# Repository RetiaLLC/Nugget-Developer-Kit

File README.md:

# WiFi Nugget Developer Kit v2.2
This repository contains KiCAD design files for the WiFi Nugget Developer Kit PCB.  The current version of this release is `2.2`.
This kit is designed to teach beginners basic hardware assembly skills, and features both through-hole and surface mount components.
<p align="center">
  <br>
  
  <br>
  <b>ESP32-S2 DevKit Components</b>
  <br>
  <br>
</p>

## Features
This kit is designed to work with the [Wemos "mini" form factor](https://www.wemos.cc/en/latest/), and accomodates breakouts for the ESP8266, ESP32-S2, and some other Espressif based board designs.
The developer kit includes:

- **Buttons** (D-Pad style, 4 Buttons)
- **RGB LED** (WS2812B NeoPixel)
- **WiFi Microcontroller** ([D1](https://www.wemos.cc/en/latest/d1/index.html)/[S2](https://www.wemos.cc/en/latest/s2/index.html)/[C3](https://www.wemos.cc/en/latest/c3/index.html) Mini)
- **Screen** (SH1106 1.3" OLED)
- **Expansion Headers** 
- **Screw Assembly*** (M2.5 Screws / Threaded Inserts)
- **3D Printed Case***

\* *We ditched the screw assembly on newer Nuggets, which use a snap-fit case.  You can find links to our case designs below.*

## Resources
- [Assembly Guide]()
- [3D printed cases](https://github.com/HakCat-Tech/WiFi-Nugget-Cases)

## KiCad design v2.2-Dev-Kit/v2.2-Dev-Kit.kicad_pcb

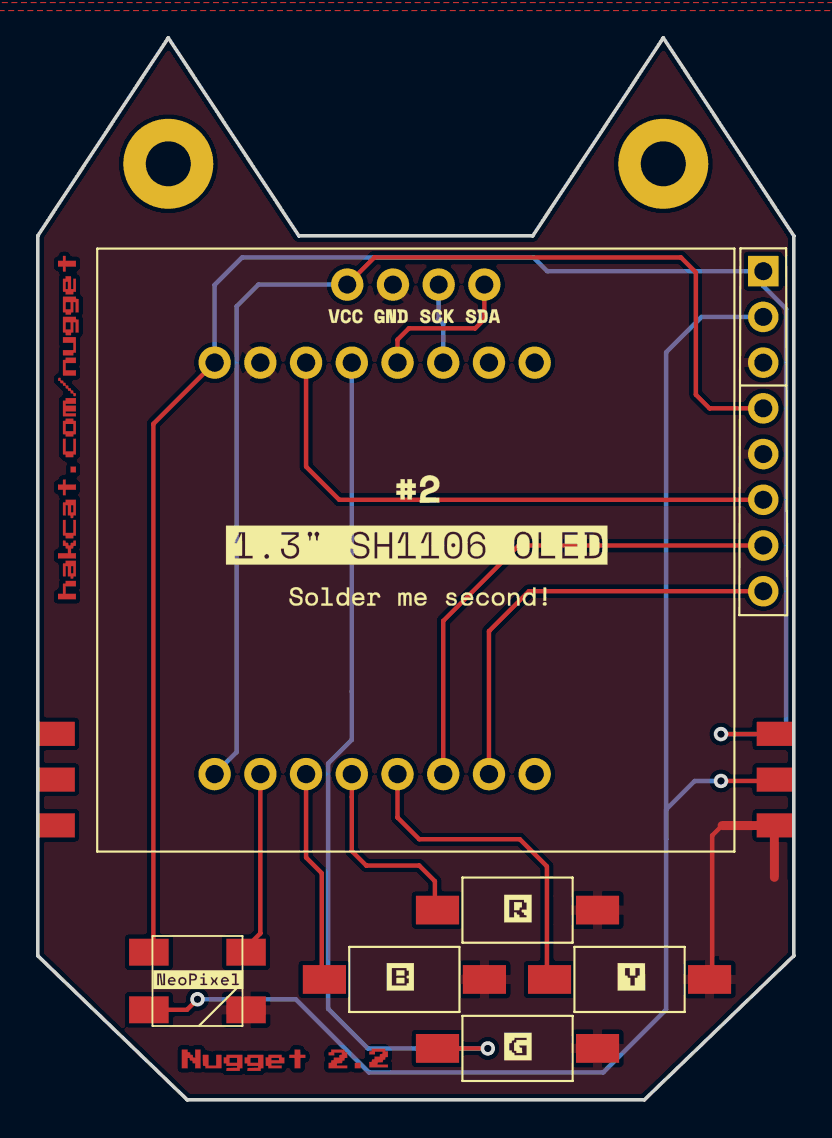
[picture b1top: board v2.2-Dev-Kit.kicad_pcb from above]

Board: 2 copper layers, 42.0 x 59.0 mm, 9 parts (1 on the bottom side), 14 nets.

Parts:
D1: WS2812B; LED_WS2812B_PLCC4_5.0x5.0mm_P3.2mm_idiot_proof
J1: 8 Pin Header; PinHeader_1x08_P2.54mm_Vertical
Ref**: Val**; Nugget-PCB-Art
SW1: Up; SW_SPST_FSMSM
SW2: Down; SW_SPST_FSMSM
SW3: Left; SW_SPST_FSMSM
SW4: Right; SW_SPST_FSMSM
U1: WeMos D1 Mini; wemos-d1-mini-with-pin-header-and-connector
U2: SH1106 OLED; SH1106-128x64-OLED

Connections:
+5V: D1.1, J1.1, U1.9
/D5: SW4.1, U1.4
/D6: SW1.1, U1.5
/D7: SW3.1, U1.6
GND: D1.3, J1.3, J1.5, SW1.2, SW2.2, SW3.2, SW4.2, U1.10, U2.2
unnamed: J1.4, U1.8, U2.1
unnamed: U1.14, U2.3
unnamed: U1.13, U2.4
unnamed: D1.2, J1.2
unnamed: D1.4, U1.7
unnamed: J1.8, U1.2
unnamed: J1.7, U1.3
unnamed: J1.6, U1.11
unnamed: SW2.1, U1.12

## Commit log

2022-11-05 add v2 Developer Kit license, readme, design files
